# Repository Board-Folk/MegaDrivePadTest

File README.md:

# Mega Drive Pad Tester

Simple testing device for Mega Drive/Genesis controllers.

Does not support the extra functionality of a 6-button pad.

## Bill of Materials

| Part                         | Quantity |
|------------------------------|----------|
| LED 5mm                      | 7        |
| Resistor 10K (THT or 0805)   | 7        |
| Resistor 270Ω (THT or 0805)  | 7        |
| SPDT slide switch            | 1        |
| Right angle DE9 (male)       | 1        |
| USB Micro port               | 1\*      |
| 2-pin header 2.54mm pitch    | 1\*      |

\* For power, either or both may be installed.

## How to Use

* Connect controller to DE9 port
* Apply +5V power though USB port or alternate power header.
* With SELECT switch in left position, LEDs will illuninate for Up, Down, Left, Right, B and C.
* With SELECT switch in right position, LEDs will illuninate for Up, Down, A and Start.
  (Left and Right will both remain illuminated, this is normal).

## License

Public domain.

## Legal

You are free to produce PCBs based on this project's designs at your own risk
and without limitation, for your own use or for sale and/or repair at a
reasonable price. Attribution is appreciated. The authors are not obliged to
provide support of any kind.

Under no circumstances will the authors be held responsible or liable in any
way for losses, damages or costs resulting from the use of the information
and/or resources of this project.

The resources are provided "as-is" without warranty of any kind, either
expressed or implied, including, but not limited to, the implied warranties
of merchantability and fitness for a particular purpose.

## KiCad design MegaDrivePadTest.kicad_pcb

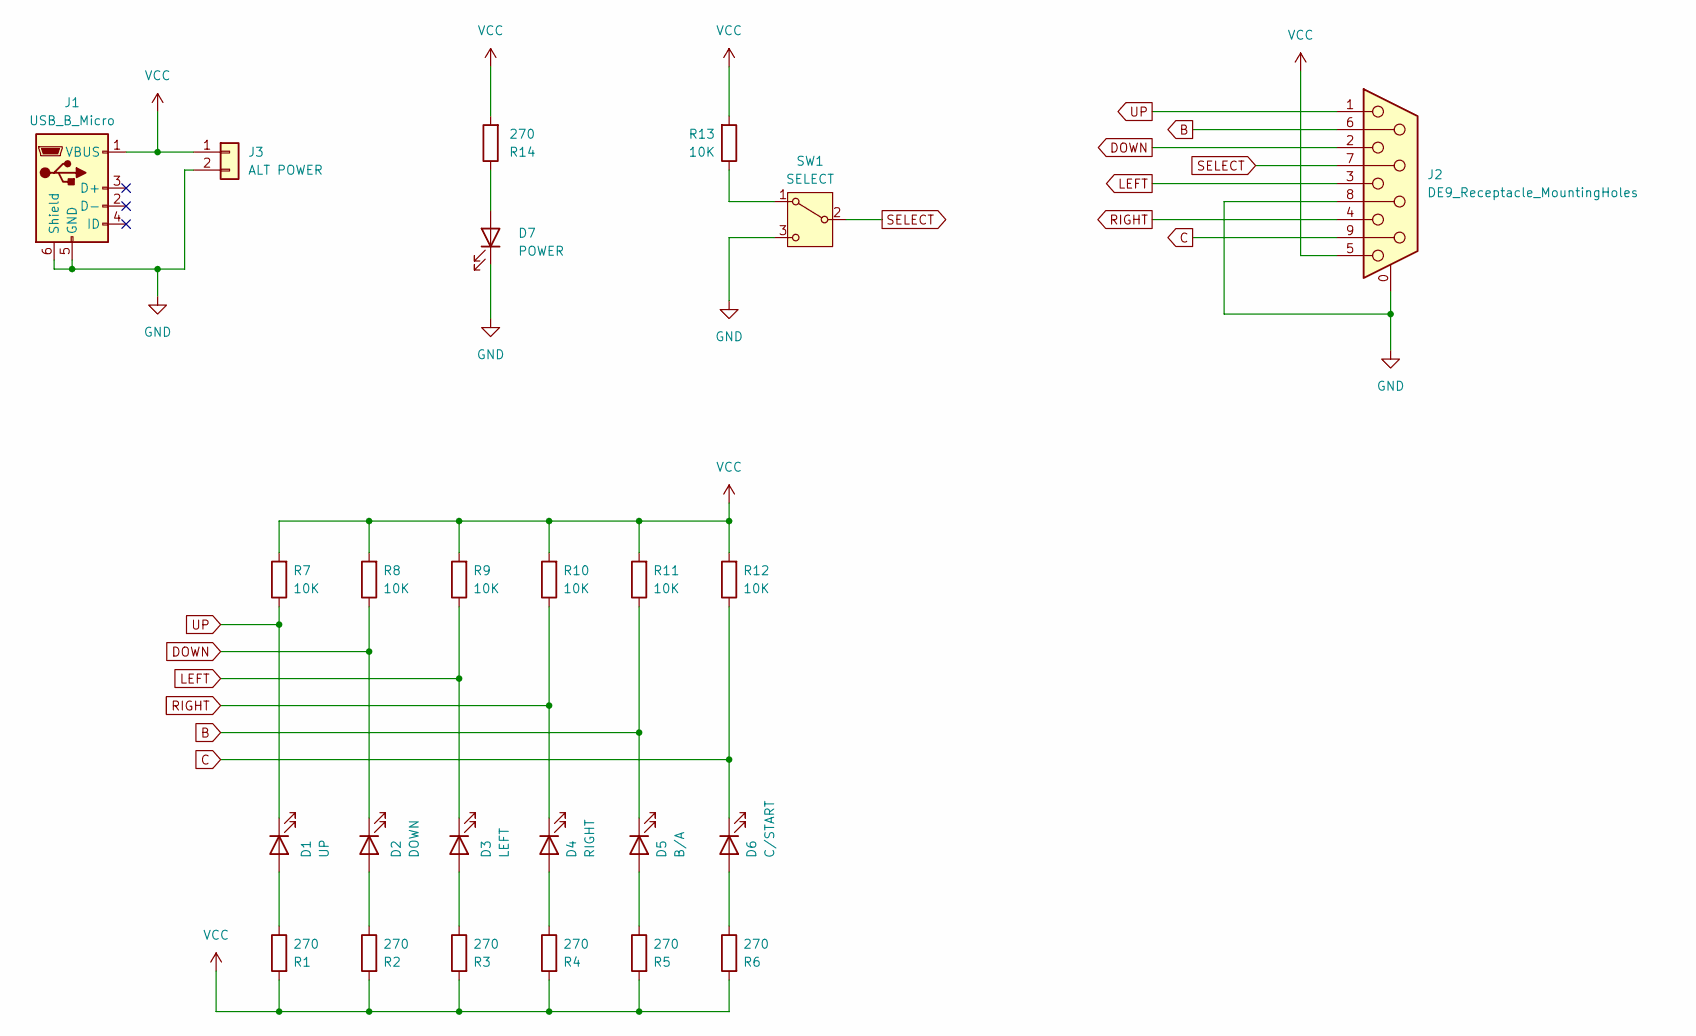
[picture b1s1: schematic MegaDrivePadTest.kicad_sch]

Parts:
D1: UP; LED_D5.0mm
D2: DOWN; LED_D5.0mm
D3: LEFT; LED_D5.0mm
D4: RIGHT; LED_D5.0mm
D5: B/A; LED_D5.0mm
D6: C/START; LED_D5.0mm
D7: POWER; LED_D5.0mm
J1: USB_B_Micro; USB_Micro-B_Amphenol_10103594-0001LF_Horizontal
J2: DE9_Receptacle_MountingHoles; DSUB-9_Male_Horizontal_P2.77x2.84mm_EdgePinOffset4.94mm_Hou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
J3: ALT POWER; PinHeader_1x02_P2.54mm_Vertical
R1, R2, R3, R4, R5, R6, R14: 270; R_Combo
R7, R8, R9, R10, R11, R12, R13: 10K; R_Combo
SW1: SELECT; Switch

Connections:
B: D5.1 (K), J2.6, R11.1
C: D6.1 (K), J2.9, R12.1
DOWN: D2.1 (K), J2.2, R8.1
GND: D7.1 (K), J1.5 (GND), J1.6 (Shield), J2.0 (PAD), J2.8, J3.2, SW1.3 (C)
LEFT: D3.1 (K), J2.3, R9.1
unnamed: D1.2 (A), R1.1
unnamed: D2.2 (A), R2.1
unnamed: D3.2 (A), R3.1
unnamed: D4.2 (A), R4.1
unnamed: D5.2 (A), R5.1
unnamed: D6.2 (A), R6.1
unnamed: D7.2 (A), R14.1
unnamed: R13.1, SW1.1 (A)
RIGHT: D4.1 (K), J2.4, R10.1
SELECT: J2.7, SW1.2 (B)
UP: D1.1 (K), J2.1, R7.1
VCC: J1.1 (VBUS), J2.5, J3.1, R1.2, R2.2, R3.2, R4.2, R5.2, R6.2, R7.2, R8.2, R9.2, R10.2, R11.2, R12.2, R13.2, R14.2

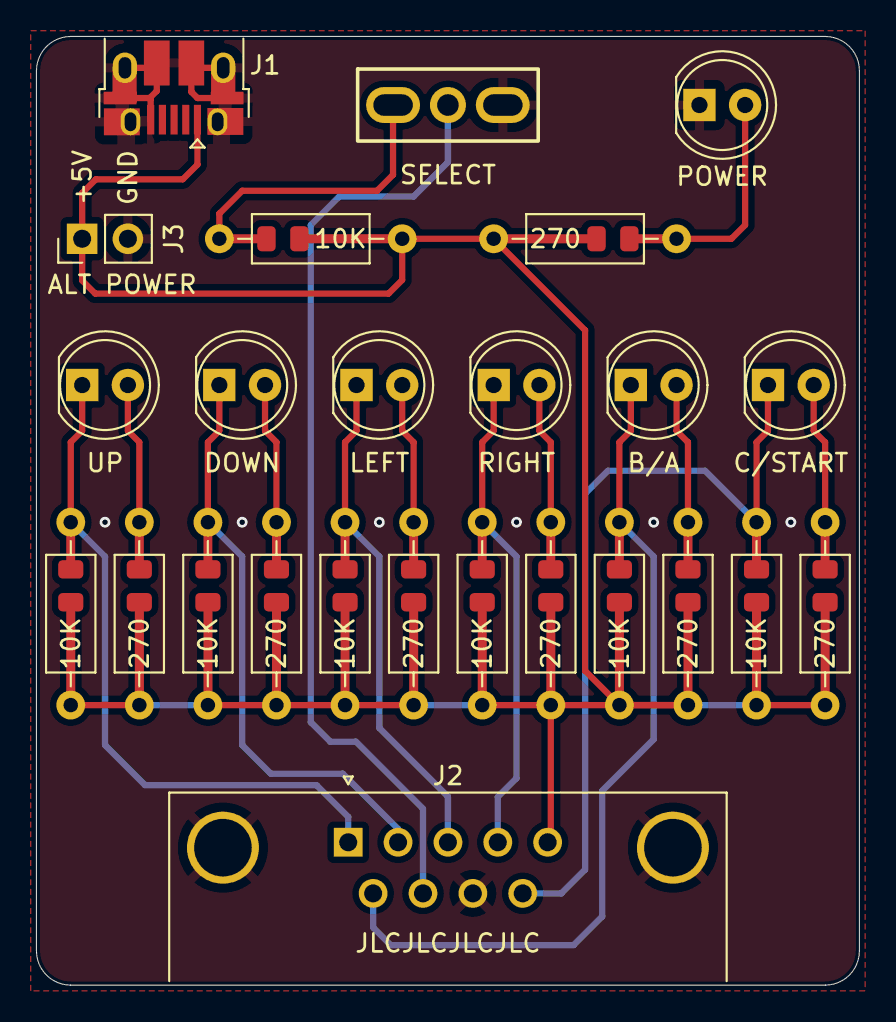
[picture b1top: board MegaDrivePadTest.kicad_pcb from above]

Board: 2 copper layers, 45.7 x 52.7 mm, 25 parts (0 on the bottom side), 17 nets.

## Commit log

2024-12-05 Move USB port to edge of PCB.
2024-12-20 Allow for wider switches.
2024-12-20 Add legal info to README.
